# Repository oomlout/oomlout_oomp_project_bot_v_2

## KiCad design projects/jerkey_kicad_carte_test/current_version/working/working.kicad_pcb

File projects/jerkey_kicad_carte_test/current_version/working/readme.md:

# kicad
 
## summary 
* id: jerkey_kicad_carte_test
* user: jerkey
* name: kicad
* board: carte_test
* repo: https://github.com/jerkey/kicad
* src_file_repo_kicad_pcb: demos/test_xil_95108/carte_test.kicad_pcb
* src_file_repo_kicad_pcb_link: https://github.com/jerkey/kicad/tree/master/demos/test_xil_95108/carte_test.kicad_pcb

* src_file_repo_sch: demos/test_xil_95108/carte_test.sch
* src_file_repo_sch_link: https://github.com/jerkey/kicad/tree/master/demos/test_xil_95108/carte_test.sch
* full details link: https://github.com/oomlout/oomlout_oomp_project_bot_v_2/tree/main/projects/jerkey_kicad_carte_test/current_version/working

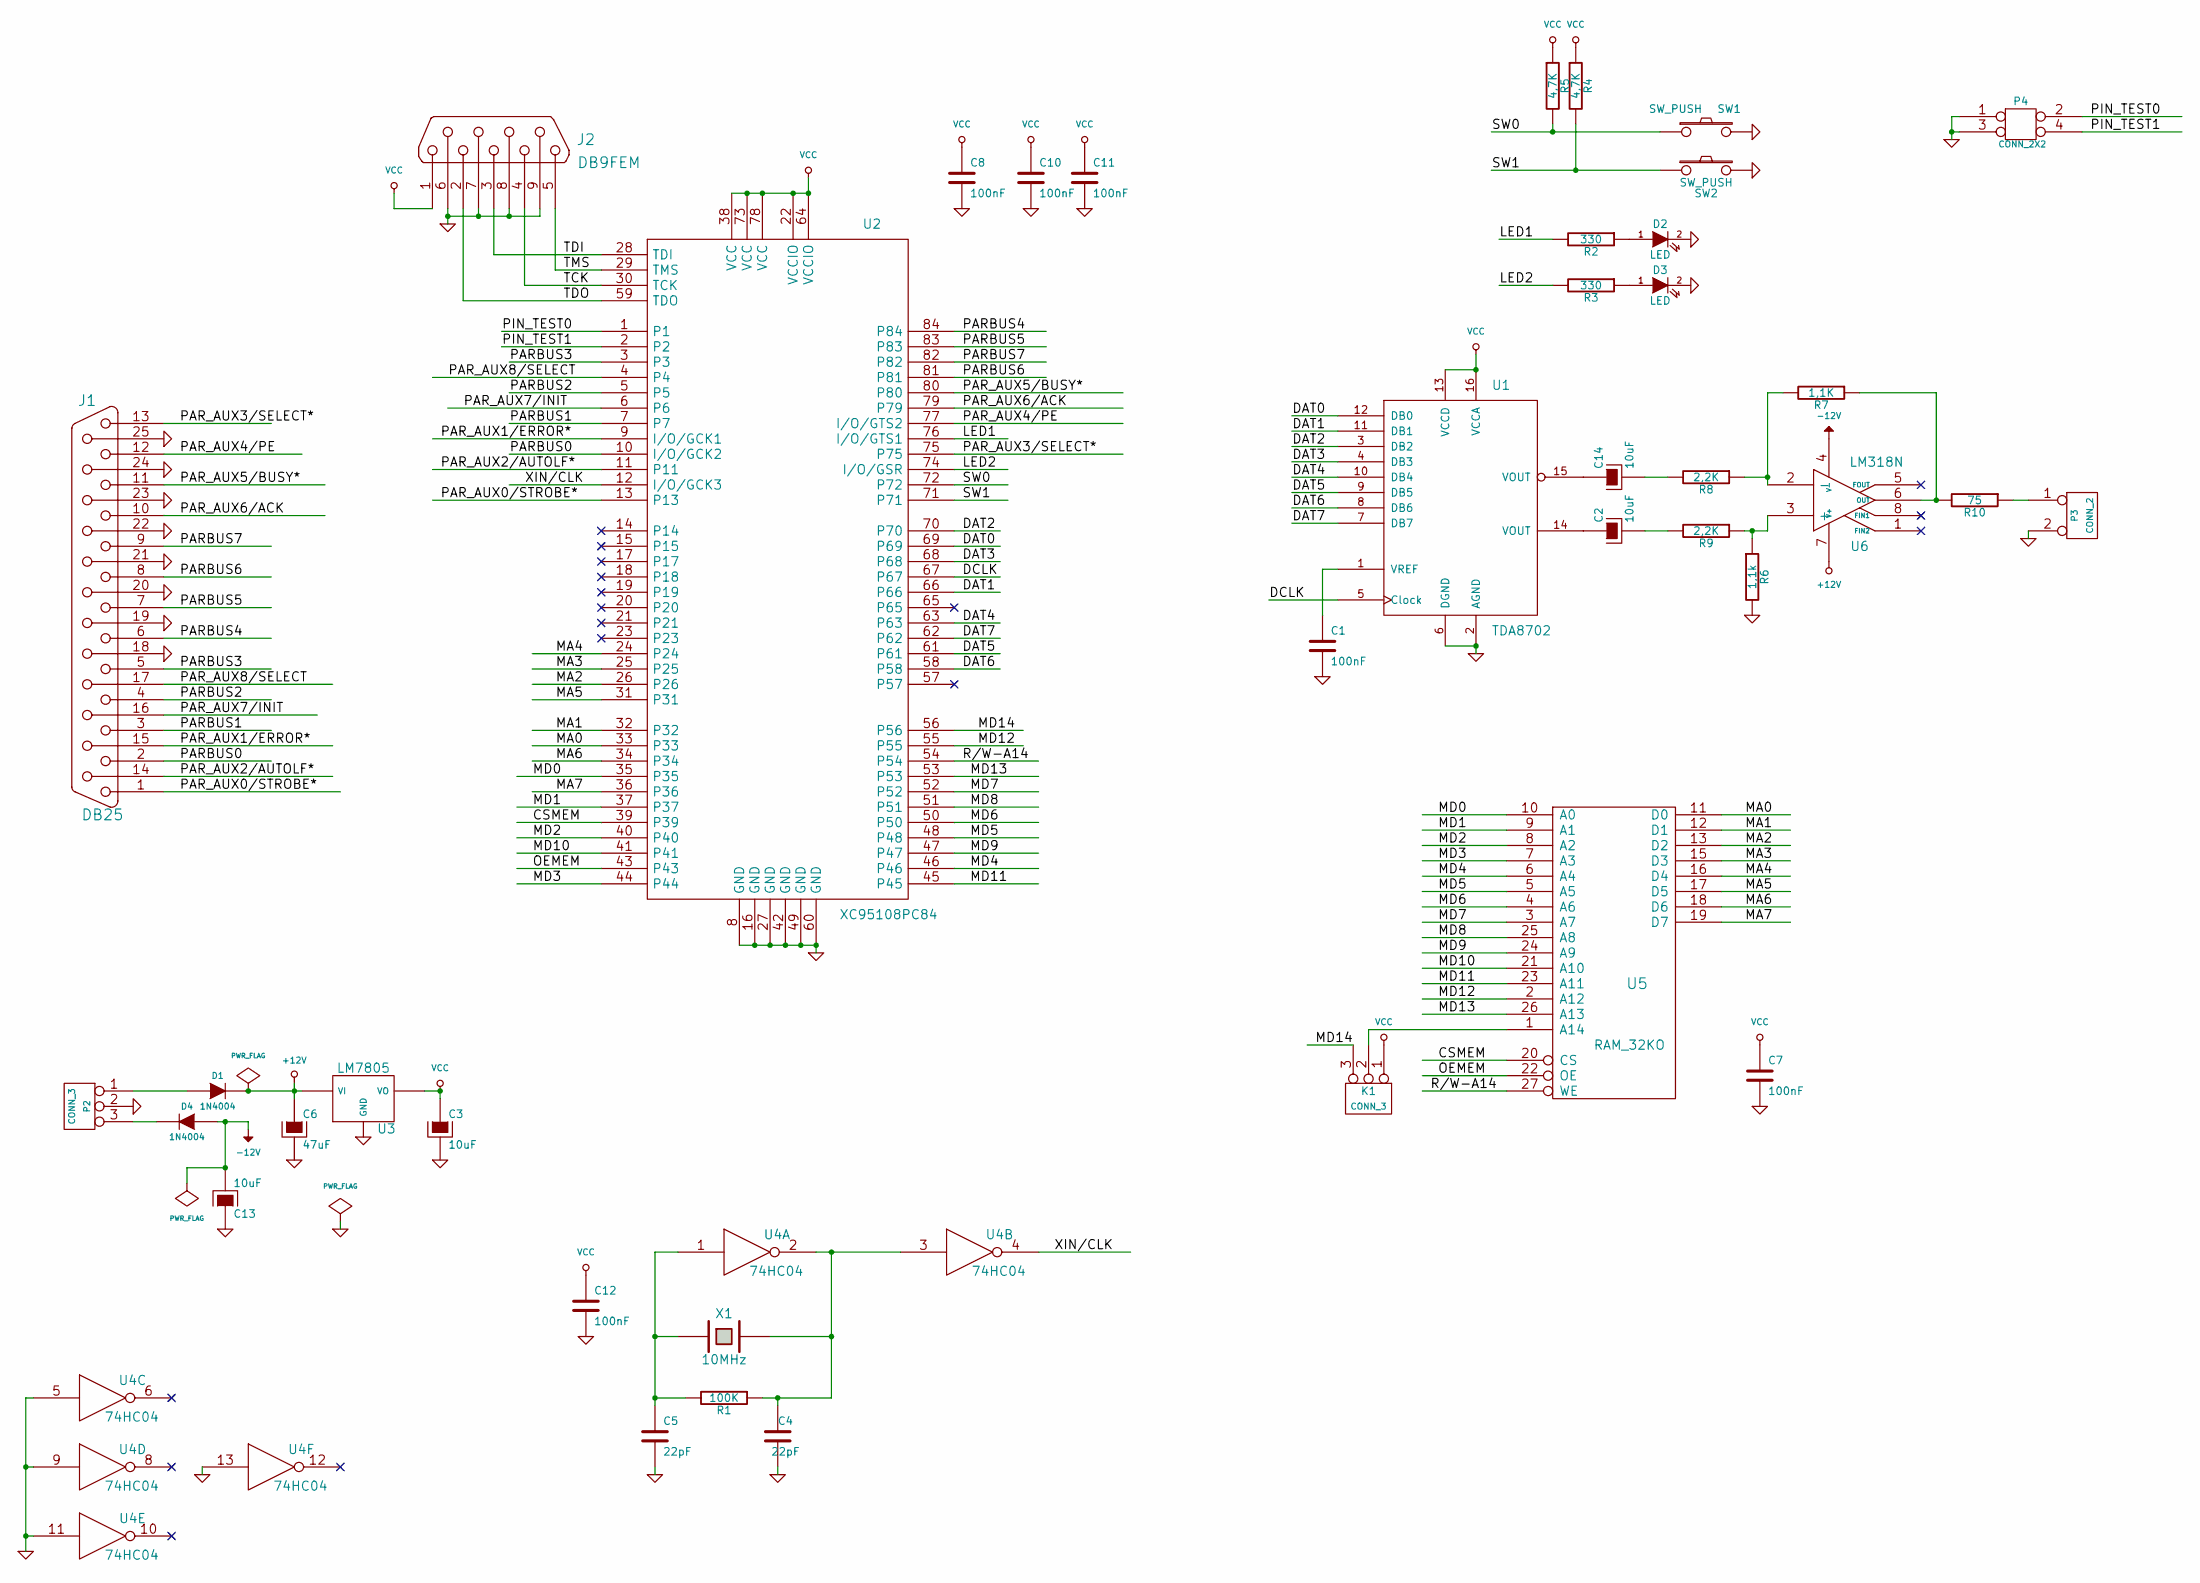
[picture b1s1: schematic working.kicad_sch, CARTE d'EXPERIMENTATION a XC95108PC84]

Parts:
C1, C7, C8, C10, C11, C12: 100nF
C2, C3, C13, C14: 10uF
C4, C5: 22pF
C6: 47uF
D1, D4: 1N4004
D2, D3: LED
J1: DB25
J2: DB9FEM
K1: CONN_3
P2: CONN_3
P3: CONN_2
P4: CONN_2X2
R1: 100K
R2, R3: 330
R4, R5: 4,7K
R6: 1,1k
R7: 1,1K
R8, R9: 2,2K
R10: 75
SW1, SW2: SW_PUSH
U1: TDA8702
U2: XC95108PC84
U3: LM7805
U4: 74HC04
U5: RAM_32KO
U6: LM318N
X1: 10MHz

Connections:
+12V: C6.1, D1.2 (K), U3.VI, U6.7 (V+)
-12V: C13.2, D4.1 (A), U6.4 (V-)
/CSMEM: U2.39, U5.20 (CS)
/DAT0: U1.12 (DB0), U2.69
/DAT1: U1.11 (DB1), U2.66
/DAT2: U1.3 (DB2), U2.70
/DAT3: U1.4 (DB3), U2.68
/DAT4: U1.10 (DB4), U2.63
/DAT5: U1.9 (DB5), U2.61
/DAT6: U1.8 (DB6), U2.58
/DAT7: U1.7 (DB7), U2.62
/DCLK: U1.5 (Clock), U2.67
/LED1: R2.2, U2.76 (I/O/GTS1)
/LED2: R3.2, U2.74 (I/O/GSR)
/MA0: U2.33, U5.11 (D0)
/MA1: U2.32, U5.12 (D1)
/MA2: U2.26, U5.13 (D2)
/MA3: U2.25, U5.15 (D3)
/MA4: U2.24, U5.16 (D4)
/MA5: U2.31, U5.17 (D5)
/MA6: U2.34, U5.18 (D6)
/MA7: U2.36, U5.19 (D7)
/MD0: U2.35, U5.10 (A0)
/MD1: U2.37, U5.9 (A1)
/MD2: U2.40, U5.8 (A2)
/MD3: U2.44, U5.7 (A3)
/MD4: U2.46, U5.6 (A4)
/MD5: U2.48, U5.5 (A5)
/MD6: U2.50, U5.4 (A6)
/MD7: U2.52, U5.3 (A7)
/MD8: U2.51, U5.25 (A8)
/MD9: U2.47, U5.24 (A9)
/MD10: U2.41, U5.21 (A10)
/MD11: U2.45, U5.23 (A11)
/MD12: U2.55, U5.2 (A12)
/MD13: U2.53, U5.26 (A13)
/MD14: K1.3, U2.56
/OEMEM: U2.43, U5.22 (OE)
/PARBUS0: J1.2, U2.10 (I/O/GCK2)
/PARBUS1: J1.3, U2.7
/PARBUS2: J1.4, U2.5
/PARBUS3: J1.5, U2.3
/PARBUS4: J1.6, U2.84
/PARBUS5: J1.7, U2.83
/PARBUS6: J1.8, U2.81
/PARBUS7: J1.9, U2.82
/PAR_AUX0/STROBE*: J1.1, U2.13
/PAR_AUX1/ERROR*: J1.15, U2.9 (I/O/GCK1)
/PAR_AUX2/AUTOLF*: J1.14, U2.11
/PAR_AUX3/SELECT*: J1.13, U2.75
/PAR_AUX4/PE: J1.12, U2.77 (I/O/GTS2)
/PAR_AUX5/BUSY*: J1.11, U2.80
/PAR_AUX6/ACK: J1.10, U2.79
/PAR_AUX7/INIT: J1.16, U2.6
/PAR_AUX8/SELECT: J1.17, U2.4
/PIN_TEST0: P4.2, U2.1
/PIN_TEST1: P4.4, U2.2
/R/W-A14: U2.54, U5.27 (WE)
/SW0: R5.2, SW1.1, U2.72
/SW1: R4.2, SW2.1, U2.71
/TCK: J2.4, U2.30 (TCK)
/TDI: J2.3, U2.28 (TDI)
/TDO: J2.2, U2.59 (TDO)
/TMS: J2.5, U2.29 (TMS)
/XIN/CLK: U2.12 (I/O/GCK3), U4.4
GND: C1.2, C3.2, C4.2, C5.2, C6.2, C7.2, C8.2, C10.2, C11.2, C12.2, C13.1, D2.2 (K), D3.2 (K), J1.18, J1.19, J1.20, J1.21, J1.22, J1.23, J1.24, J1.25, J2.6, J2.7, J2.8, J2.9, P2.2 (PM), P3.2 (PM), P4.1, P4.3, R6.2, SW1.2, SW2.2, U1.2 (AGND), U1.6 (DGND), U2.8 (GND), U2.16 (GND), U2.27 (GND), U2.42 (GND), U2.49 (GND), U2.60 (GND), U3.GND, U4.5, U4.7 (GND), U4.9, U4.11, U4.13, U5.14 (GND)
unnamed: C1.1, U1.1 (VREF)
unnamed: C2.1, U1.14 (VOUT)
unnamed: C2.2, R9.2
unnamed: C4.1, R1.1, U4.2, U4.3, X1.2
unnamed: C5.1, R1.2, U4.1, X1.1
unnamed: C14.1, U1.15 (VOUT)
unnamed: C14.2, R8.2
unnamed: D1.1 (A), P2.1
unnamed: D2.1 (A), R2.1
unnamed: D3.1 (A), R3.1
unnamed: D4.2 (K), P2.3
unnamed: K1.2 (PM), U5.1 (A14)
unnamed: P3.1, R10.1
unnamed: R6.1, R9.1, U6.3 (+)
unnamed: R7.2, R8.1, U6.2 (-)
unnamed: R7.1, R10.2, U6.6 (OUT)
VCC: C3.1, C7.1, C8.1, C10.1, C11.1, C12.1, J2.1, K1.1, R4.1, R5.1, U1.13 (VCCD), U1.16 (VCCA), U2.22 (VCCIO), U2.38 (VCC), U2.64 (VCCIO), U2.73 (VCC), U2.78 (VCC), U3.VO, U4.14 (VCC), U5.28 (VCC)

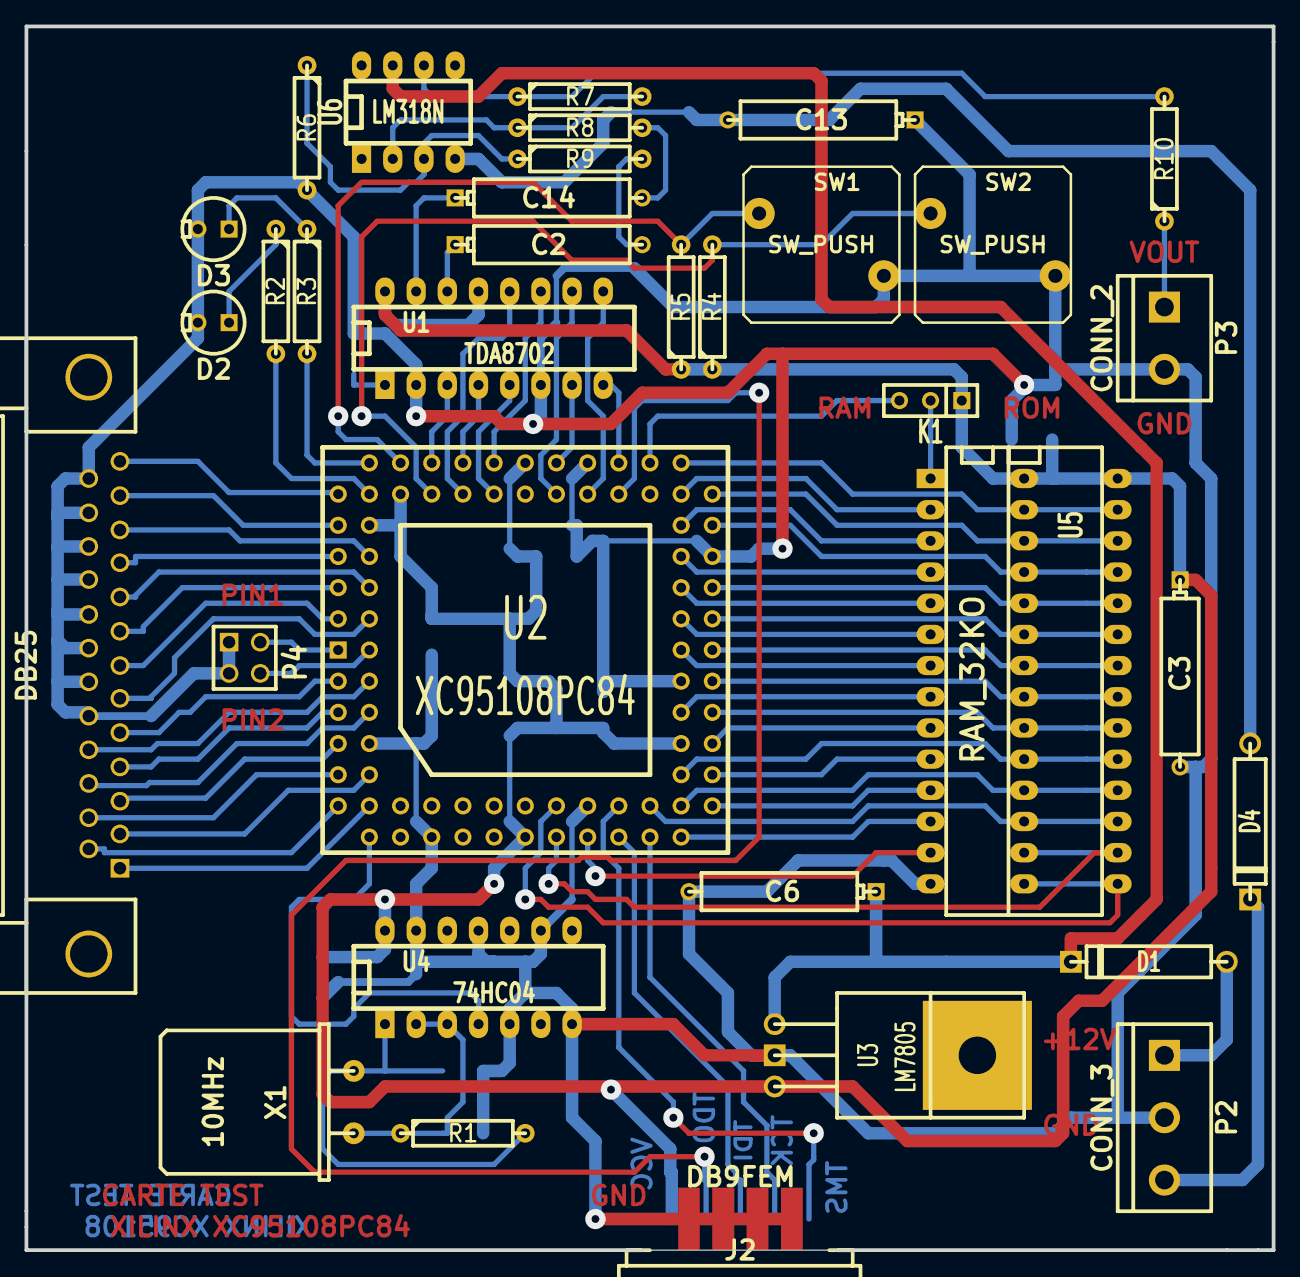
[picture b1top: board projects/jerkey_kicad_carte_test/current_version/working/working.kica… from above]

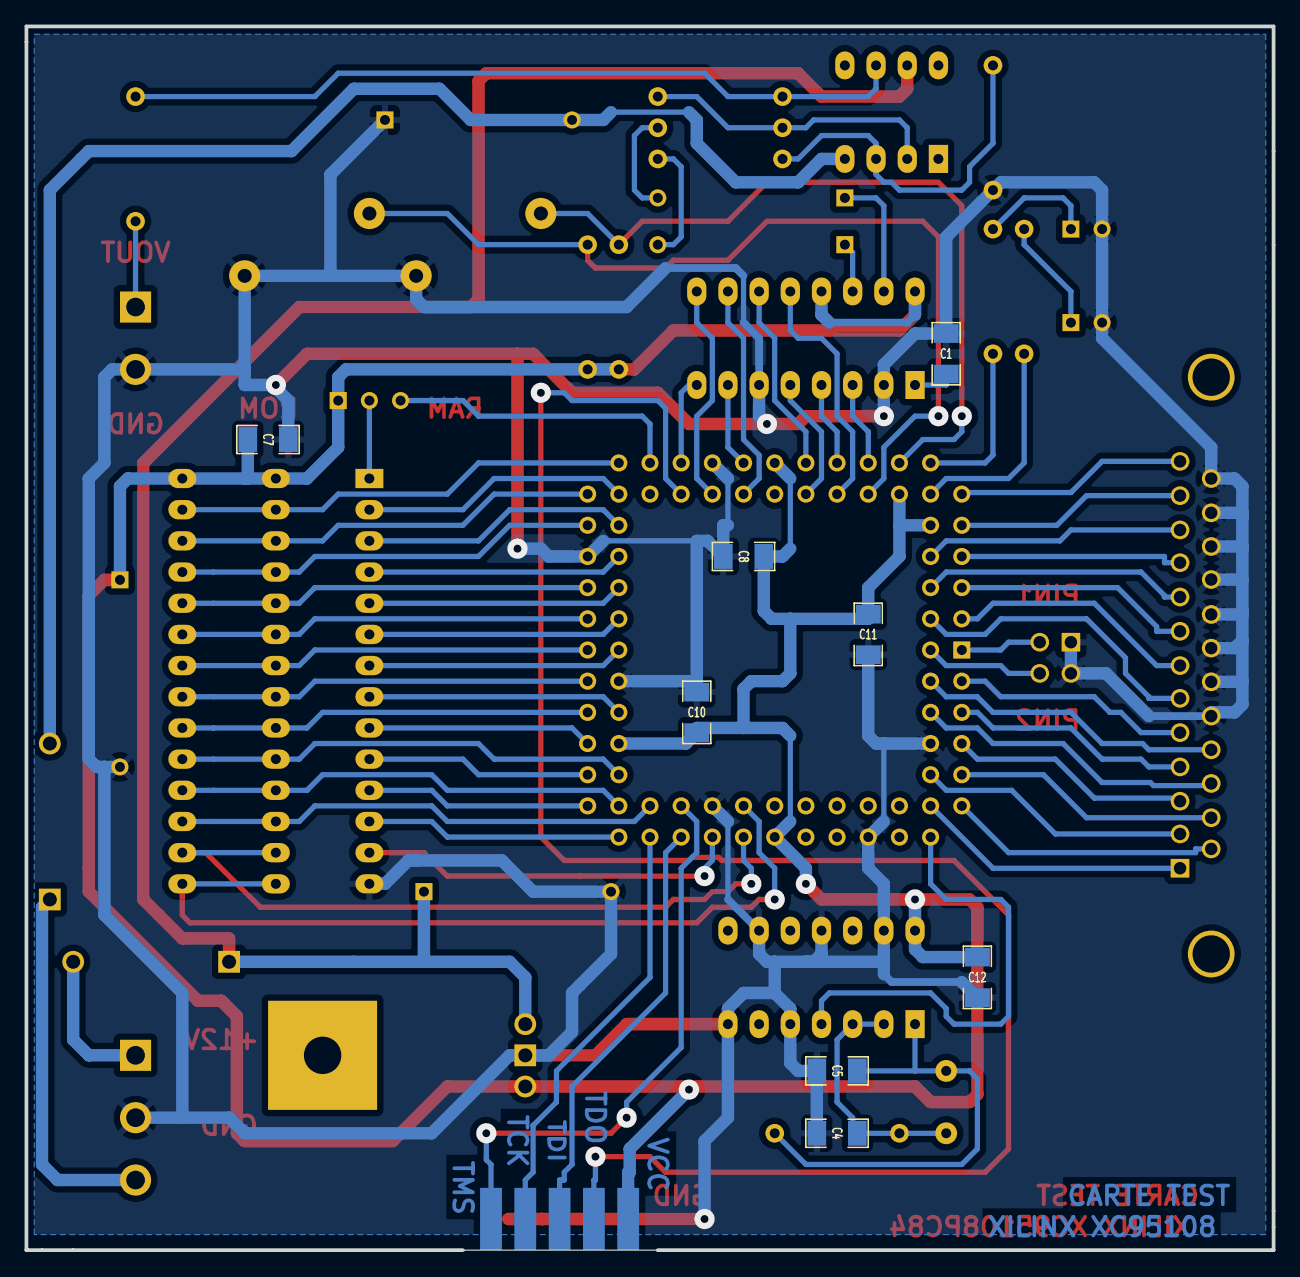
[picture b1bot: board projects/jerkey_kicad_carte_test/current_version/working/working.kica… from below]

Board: 2 copper layers, 101.6 x 99.7 mm, 42 parts (8 on the bottom side), 83 nets.

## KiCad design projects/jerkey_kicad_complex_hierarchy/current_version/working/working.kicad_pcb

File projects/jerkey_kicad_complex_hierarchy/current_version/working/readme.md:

# kicad
 
## summary 
* id: jerkey_kicad_complex_hierarchy
* user: jerkey
* name: kicad
* board: complex_hierarchy
* repo: https://github.com/jerkey/kicad
* src_file_repo_kicad_pcb: qa/data/complex_hierarchy.kicad_pcb
* src_file_repo_kicad_pcb_link: https://github.com/jerkey/kicad/tree/master/qa/data/complex_hierarchy.kicad_pcb

* src_file_repo_sch: demos/test_xil_95108/carte_test.sch
* src_file_repo_sch_link: https://github.com/jerkey/kicad/tree/master/demos/test_xil_95108/carte_test.sch
* full details link: https://github.com/oomlout/oomlout_oomp_project_bot_v_2/tree/main/projects/jerkey_kicad_complex_hierarchy/current_version/working

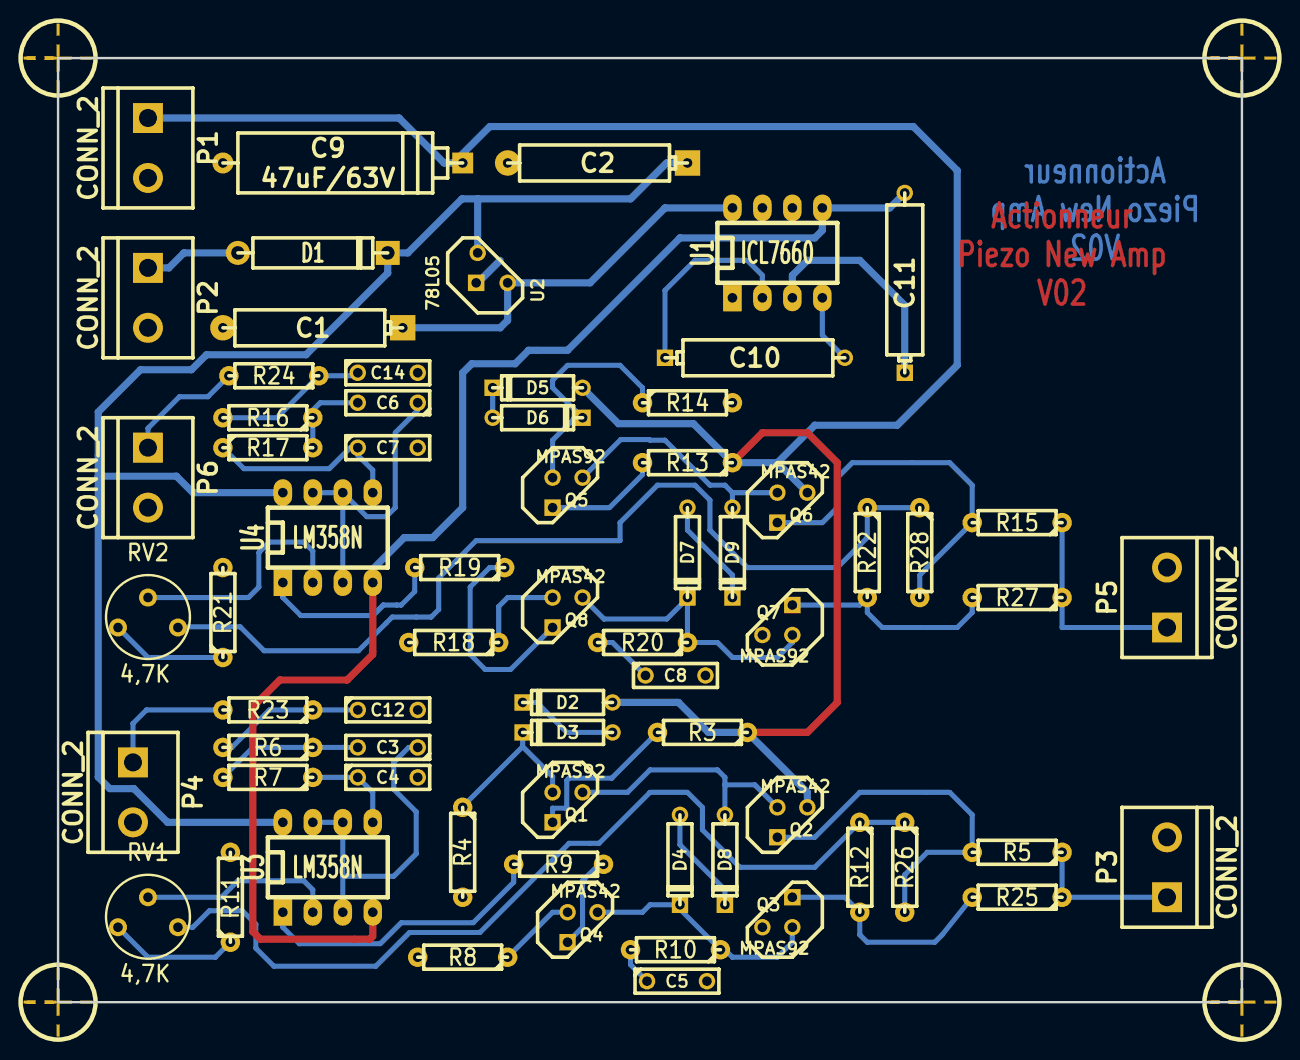
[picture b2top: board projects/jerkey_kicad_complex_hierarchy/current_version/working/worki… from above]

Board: 2 copper layers, 100.3 x 80.0 mm, 72 parts (0 on the bottom side), 50 nets.

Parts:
C1: 47uF; CP6
C2: 47uF/20V; CP6
C3, C6: 15nF; C2
C4, C7: 4,7nF; C2
C5, C8: 820pF; C2
C9: 47uF/63V; CP8
C10, C11: 10uF; CP6
C12, C14: 150nF; C2
D1: 1N4007; D5
D2, D3, D4, D5, D6, D7, D8, D9: 1N4148; D3
MIRE: *; MIRE
MIRE#2, MIRE#3, MIRE#4: *; MIRE
P1, P2, P3, P4, P5, P6: CONN_2; bornier2
Q1, Q3, Q5, Q7: MPAS92; TO92-CBE
Q2, Q4, Q6, Q8: MPAS42; TO92-CBE
R3, R13: 470; R3-LARGE_PADS
R4, R12, R14, R22, R26, R28: 220K; R3-LARGE_PADS
R5, R15, R25, R27: 47; R3-LARGE_PADS
R6, R7, R16, R17: 22K; R3-LARGE_PADS
R8, R9, R18, R19, R23, R24: 1K; R3-LARGE_PADS
R10, R20: 5,6K; R3-LARGE_PADS
R11, R21: 4,7K; R3-LARGE_PADS
RV1, RV2: 4,7K; RV2
U1: ICL7660; DIP-8__300_ELL
U2: 78L05; LM78LXX
U3, U4: LM358N; DIP-8__300_ELL

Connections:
+12V: C2.1, D1.2, U2.VI, U3.8, U4.8
-VAA: C11.2, U1.5, U3.4, U4.4
/12Vext: D1.1, P2.1
/ampli_h1: C3.1, U3.3, U3.6, U3.7
/ampli_h2: C6.1, U4.3, U4.6, U4.7
/ampli_h3: P3.1, R5.1, R25.1
/ampli_h4: P4.1, R23.2
/ampli_h5: P5.1, R15.1, R27.1
/ampli_h6: P6.1, R24.2
/ampli_h7: R12.1, R26.1, RV1.3
/ampli_h8: R22.1, R28.1, RV2.3
GND: C1.2, C2.2, C4.2, C5.2, C7.2, C8.2, C9.2, C11.1, C12.2, C14.2, P1.2, P2.2, P3.2, P4.2, P5.2, P6.2, Q3.C, Q7.C, R4.2, R8.2, R11.2, R14.2, R18.2, R21.2, U1.3, U2.GND
HT: C9.1, D2.1, D5.1, P1.1, Q2.C, Q6.C, R3.1, R13.1
unnamed: C10.2, U1.4
unnamed: C10.1, U1.2
unnamed: Q4.E, R9.1
unnamed: D2.2, D3.1
unnamed: C3.2, R6.1, R7.2
unnamed: C12.1, R6.2, R23.1
unnamed: C5.1, R10.2
unnamed: Q2.E, R5.2, R26.2
unnamed: Q3.E, R12.2, R25.2
unnamed: R11.1, RV1.1
unnamed: D3.2, Q1.B, R4.1
unnamed: Q4.B, R8.1
unnamed: R9.2, U3.1
unnamed: RV1.2, U3.2
unnamed: D4.1, D8.2
unnamed: C4.1, R7.1, U3.5
unnamed: D4.2, Q3.B, Q4.C, R10.1
unnamed: D8.1, Q1.C, Q2.B
unnamed: Q1.E, R3.2
unnamed: Q8.E, R19.1
unnamed: D5.2, D6.1
unnamed: C6.2, R16.1, R17.2
unnamed: C14.1, R16.2, R24.1
unnamed: C8.1, R20.2
unnamed: Q6.E, R15.2, R28.2
unnamed: Q7.E, R22.2, R27.2
unnamed: R21.1, RV2.1
unnamed: D6.2, Q5.B, R14.1
unnamed: Q8.B, R18.1
unnamed: R19.2, U4.1
unnamed: RV2.2, U4.2
unnamed: D7.1, D9.2
unnamed: C7.1, R17.1, U4.5
unnamed: D7.2, Q7.B, Q8.C, R20.1
unnamed: D9.1, Q5.C, Q6.B
unnamed: Q5.E, R13.2
VCC: C1.1, U1.8, U2.VO

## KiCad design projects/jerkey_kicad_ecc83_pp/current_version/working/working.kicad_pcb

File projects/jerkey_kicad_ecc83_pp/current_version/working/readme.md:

# kicad
 
## summary 
* id: jerkey_kicad_ecc83_pp
* user: jerkey
* name: kicad
* board: ecc83_pp
* repo: https://github.com/jerkey/kicad
* src_file_repo_kicad_pcb: demos/ecc83/ecc83-pp.kicad_pcb
* src_file_repo_kicad_pcb_link: https://github.com/jerkey/kicad/tree/master/demos/ecc83/ecc83-pp.kicad_pcb

* src_file_repo_sch: demos/ecc83/ecc83-pp.sch
* src_file_repo_sch_link: https://github.com/jerkey/kicad/tree/master/demos/ecc83/ecc83-pp.sch
* full details link: https://github.com/oomlout/oomlout_oomp_project_bot_v_2/tree/main/projects/jerkey_kicad_ecc83_pp/current_version/working

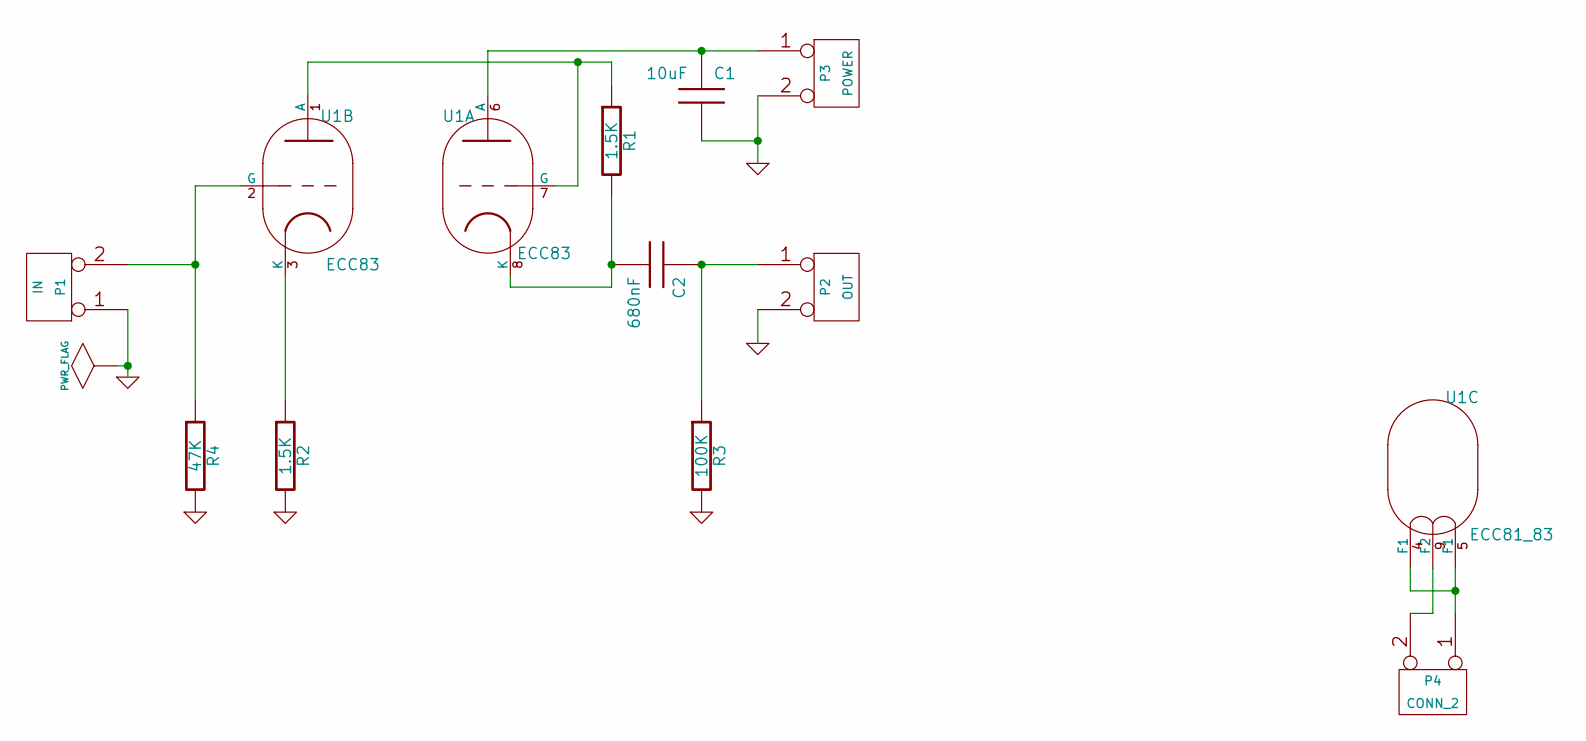
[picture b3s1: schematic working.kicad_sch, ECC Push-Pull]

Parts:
C1: 10uF
C2: 680nF
P1: IN
P2: OUT
P3: POWER
P4: CONN_2
R1, R2: 1.5K
R3: 100K
R4: 47K
U1: ECC83; VALVE-NOVAL_P

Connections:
GND: C1.2, P1.1, P2.2 (PM), P3.2 (PM), R2.2, R3.2, R4.2
unnamed: R1.1, U1.1 (A), U1.7 (G)
unnamed: P4.2 (PM), U1.9 (F2)
unnamed: P1.2 (PM), R4.1, U1.2 (G)
unnamed: R2.1, U1.3 (K)
unnamed: C2.1, P2.1, R3.1
unnamed: P4.1, U1.4 (F1), U1.5 (F1)
unnamed: C1.1, P3.1, U1.6 (A)
unnamed: C2.2, R1.2, U1.8 (K)

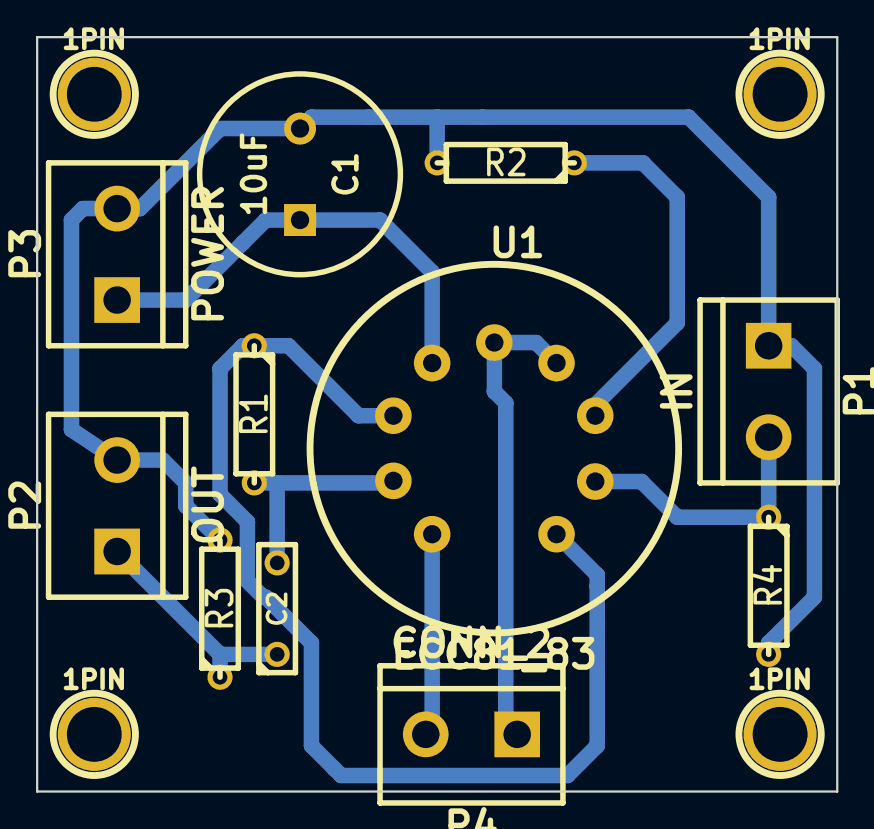
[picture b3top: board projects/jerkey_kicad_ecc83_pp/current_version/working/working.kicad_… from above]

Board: 2 copper layers, 44.5 x 41.9 mm, 15 parts (0 on the bottom side), 9 nets.

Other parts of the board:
1PIN, 1PIN#2, 1PIN#3, 1PIN#4: P***; 1pin

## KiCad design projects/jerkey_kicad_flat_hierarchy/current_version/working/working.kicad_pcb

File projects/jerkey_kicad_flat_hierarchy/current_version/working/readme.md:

# kicad
 
## summary 
* id: jerkey_kicad_flat_hierarchy
* user: jerkey
* name: kicad
* board: flat_hierarchy
* repo: https://github.com/jerkey/kicad
* src_file_repo_kicad_pcb: demos/flat_hierarchy/flat_hierarchy.kicad_pcb
* src_file_repo_kicad_pcb_link: https://github.com/jerkey/kicad/tree/master/demos/flat_hierarchy/flat_hierarchy.kicad_pcb

* src_file_repo_sch: demos/flat_hierarchy/flat_hierarchy.sch
* src_file_repo_sch_link: https://github.com/jerkey/kicad/tree/master/demos/flat_hierarchy/flat_hierarchy.sch
* full details link: https://github.com/oomlout/oomlout_oomp_project_bot_v_2/tree/main/projects/jerkey_kicad_flat_hierarchy/current_version/working

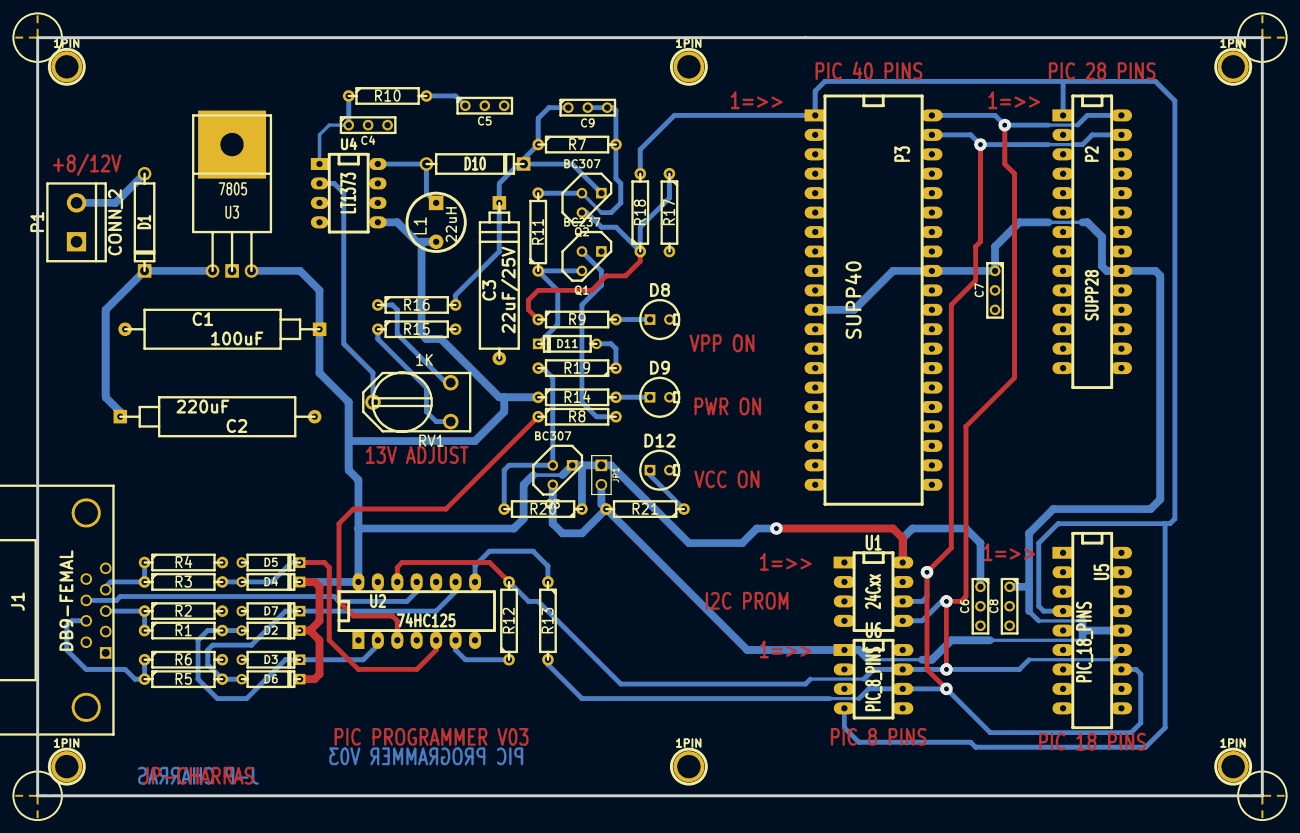
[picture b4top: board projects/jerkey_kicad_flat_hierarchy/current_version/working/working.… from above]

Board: 2 copper layers, 160.0 x 99.1 mm, 68 parts (0 on the bottom side), 34 nets.

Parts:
1PIN, 1PIN#2, 1PIN#3, 1PIN#4, 1PIN#5, 1PIN#6: P***; 1pin
C1: 100uF; CP10
C2: 220uF; CP10
C3: 22uF/25V; CP8
C4: 0; C1-1
C5: 10nF; C1-1
C6, C7, C8: 100nF; C1-1
C9: 22OnF; C1-1
D1: 1N4004; D5
D2, D3, D4, D5, D6, D7, D11: BAT43; D3
D8: RED-LED; LEDV
D9: GREEN-LED; LEDV
D10: SCHOTTKY; D5
D12: YELLOW-LED; LEDV
J1: DB9-FEMAL; DB9FC
JP1: JUMPER; PIN_ARRAY_2X1
L1: 22uH; INDUCTOR_V
MIRE: *; MIRE
MIRE#2, MIRE#3, MIRE#4: *; MIRE
P1: CONN_2; bornier2
P2: SUPP28; 28DIP-ELL300
P3: SUPP40; 40DIP-ELL600
Q1: BC237; TO92
Q2, Q3: BC307; TO92
R1, R2, R3, R4, R5, R6, R7: 10K; R4
R8: 1K; R4
R9, R19, R20: 2.2K; R4
R10: 5,1K; R4
R11, R17: 22K; R4
R12, R13, R14, R21: 470; R4
R15: 6.2K; R4
R16: 62K; R4
R18: 220; R4
RV1: 1K; RV2X4
U1: 24Cxx; 8DIP-ELL300
U2: 74HC125; 14DIP-ELL300
U3: 7805; LM78XX
U4: LT1373; 8DIP-ELL300
U5: PIC_18_PINS; 18DIP-ELL300
U6: PIC_8_PINS; 8DIP-ELL300

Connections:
/pic_programmer/CTS: J1.8, U2.11
/pic_programmer/PC-DATA-OUT: J1.4, R3.1, R4.1
/pic_programmer/RTS: J1.7, R5.1, R6.1
/pic_programmer/TXD: J1.3, R1.1, R2.1
/sockets/CLOCK-RB6: P2.27, P3.39, R13.2, U1.6, U5.12, U6.6
/sockets/DATA-RB7: P2.28, P3.40, R12.2, U1.5, U2.12, U5.13, U6.7
/sockets/VCC_PIC: C7.1, C8.1, JP1.2, P2.20, P3.11, P3.32, Q3.3, R21.2, U5.14, U6.1
/sockets/VPP-MCLR: P2.1, P3.1, U5.4, U6.4
GND: C1.2, C2.2, C3.2, C4.2, C5.2, C6.2, C7.2, C8.2, D3.1, D5.1, D7.1, D8.2, D9.2, D12.2, J1.5, P1.1, P2.8, P2.19, P3.8, P3.12, P3.31, Q1.1, R2.2, R4.2, R6.2, R15.2, R17.2, U1.1, U1.2, U1.3, U1.4, U2.1, U2.4, U2.7, U2.10, U2.13, U3.GND, U4.6, U4.7, U5.5, U6.8
unnamed: R12.1, U2.6
unnamed: R13.1, U2.8
unnamed: R8.1, U2.3
unnamed: Q1.2, R8.2
unnamed: D8.1, R9.2
unnamed: D1.1, P1.2
unnamed: D9.1, R14.2
unnamed: C5.1, R10.2
unnamed: C4.1, R10.1, U4.1
unnamed: D10.1, L1.1, U4.8
unnamed: R15.1, RV1.1
unnamed: R16.1, RV1.3
unnamed: RV1.2, U4.2
unnamed: Q3.2, R19.2, R20.2
unnamed: D12.1, R21.1
unnamed: D11.1, R19.1
unnamed: D11.2, Q1.3, R11.1
unnamed: Q2.3, R9.1, R17.1, R18.1
unnamed: D2.1, D3.2, R1.2, U2.2
unnamed: C2.1, D1.2, U3.VI
unnamed: C9.2, Q2.2, R7.2, R11.2
unnamed: D6.1, D7.2, R5.2, U2.9
unnamed: D4.1, D5.2, R3.2, U2.5
VCC: C1.1, C6.1, D2.2, D4.2, D6.2, JP1.1, L1.2, Q3.1, R14.1, R20.1, U1.8, U2.14, U3.VO, U4.5
VPP: C3.1, C9.1, D10.2, Q2.1, R7.1, R16.2
